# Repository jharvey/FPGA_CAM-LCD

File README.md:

# FPGA_CAM-LCD: single-board FPGA monocular

A hand-held monocular on one PCB, based on a stripped ULX3S:

- Lattice ECP5-85F FPGA, SDRAM, flash, ESP32-S3 (WiFi, USB, programming), SD card
- OV7670 camera module on the scene side, Newhaven 2.1" round TFT (NHD-2.1-480480AF-ASXP) on the eye side
- Three 18650 cells, each hot-swappable through its own quarter-turn cap, plus USB-C charging
- 3D-printed case with a 1/4-20 tripod thread

## Where things stand (2026-11-27)

| Area | State |
|---|---|
| Schematic | Frozen, with later additions listed in `doc/constraints/schematic_freeze.md` |
| PCB | Routed. KiCad DRC: 0 errors, 0 unconnected (branch `merged-board`) |
| Battery end blocks | One common machined aluminium block at all three cells, MS3181-16 bayonet caps. Mounting-hole pattern still under review |
| Case | Draft 4 modelled (not printed yet): two shells, two cell cradles, snap-in buttons, camera screwed to the lid |
| Ordering | **Not ready.** See "Open before ordering" in `ROADMAP.md` |
| FPGA and software | Written and tested in simulation only, no board exists. One bitstream (camera to TFT, overlay with text and graphics, sensor bridge) that meets timing; the ESP32 software (hub, pages, phone page) runs under MicroPython on a PC. `doc/DEVELOPER_GUIDE.md` |

**Try it without hardware** (Python 3): `python firmware/sim/fcl_sim.py --web 8080`, then open `http://127.0.0.1:8080`.
Start reading at `doc/QUICK_START.md`.

## Branches

- `merged-board`: the newest board and case. Open `FCL.kicad_pro` here.
- `monocular-strip`: the long-running design branch. `merged-board` has not been merged back into it yet.
- `battery-blocks`, `j7-vertical-wip`: the two lines of work that were combined into `merged-board`. Kept for history.
- `master`: the original ULX3S files.

## Documents

| Document | What it covers |
|---|---|
| `ROADMAP.md` | Decisions, phase status, dated change log, open items |
| `AI_GUIDE.md` | Working rules for an AI assistant or a new contributor |
| `case/README.md` | How to print, assemble and regenerate the case; hardware list |
| `docs/mech/README.md` | Battery end block: machining drawing and editable models |
| `docs/mech/freecad/README.md`, `case/freecad/README.md` | The FreeCAD files |
| `doc/constraints/camera_display_pinmap.md` | FPGA pins for the display, camera and user I/O |
| `doc/constraints/schematic_freeze.md` | Schematic freeze record and what changed after it |
| `doc/BRINGUP.md` (`.pdf`) | First power-up checklist (first article): test points, rails, programming, stage-by-stage checks |
| `doc/PRODUCTION_TEST.md` | Short per-board check once the design is validated, compared with BRINGUP golden values |
| `doc/QUICK_START.md` (`.pdf`) | One page: buttons, pages, first use, the PC tools |
| `doc/USER_MANUAL.md` | Using the unit: buttons, the screen and its graphics, the Level / Height / Bearing / Survey pages, menu, phone page, updates over Wi-Fi, logging, calibration (pictures in `doc/manual/`) |
| `doc/TROUBLESHOOTING.md` | What to look at, by symptom |
| `doc/DEVELOPER_GUIDE.md` | Software layers, writing a page of your own, graphics, scripting from a PC, the phone page's addresses, FPGA builds and clocks, tests |
| `doc/lessons/README.md` | Six lessons with the simulator: readings, slopes, heights, the compass, a room plan, a page of your own |
| `doc/FIRMWARE_GUIDE.md` | Reference made from a simulator run: USB stream, dashboard, LCD overlay, commands (pictures in `doc/fw/`) |
| `fpga/prebuilt/` | Stored build outputs: the three bitstreams, intermediates, checksums, tool versions, timing, test logs. `python fpga/make_prebuilt.py --check` compares your build with them |
| `fpga/bridge/`, `fpga/osd/`, `fpga/full/` | FPGA bridge to the ESP32 (sensors, ADC, servos, buttons), the LCD overlay, and the full design with its whole-design simulation |
| `doc/PROBE_POINTS.md` | Bare-copper probe vias on the back: spare FPGA balls, spare ESP32 pins, key nets (map: `doc/probe_points.png`) |
| `doc/jlc_check_2026-11-22.md` | JLCPCB build check (a dated snapshot; see the note at its top) |
| `fpga/IO_REMAP.md`, `fpga/ESP32_PINS.md` | FPGA and ESP32 pin maps; the camera project's clocks and what was changed in it |
| `mechanical.kicad_sch` | Mechanical bill of materials (screws, caps, springs, printed and machined parts) |

`doc/MANUAL.md`, `doc/MINIMAL.md`, `doc/TODO.txt` and the other files in `doc/` come from the original ULX3S project and describe that board, not this one.

## Phase order (do not skip)

1. Cleanup / hierarchy (done / finishing)
2. Power input redesign (3×18650)
3. Camera + display connectors/sheets
4. Mechanical outline / placement
5. BOM + JLCPCB

## When unsure

- Ask before deleting anything on `power`, `usb`, `ram`, `flash`, or `wifi`.
- Prefer “mark for deletion” + commit message over silent large deletes.
- Reference `ROADMAP.md` for locked decisions.

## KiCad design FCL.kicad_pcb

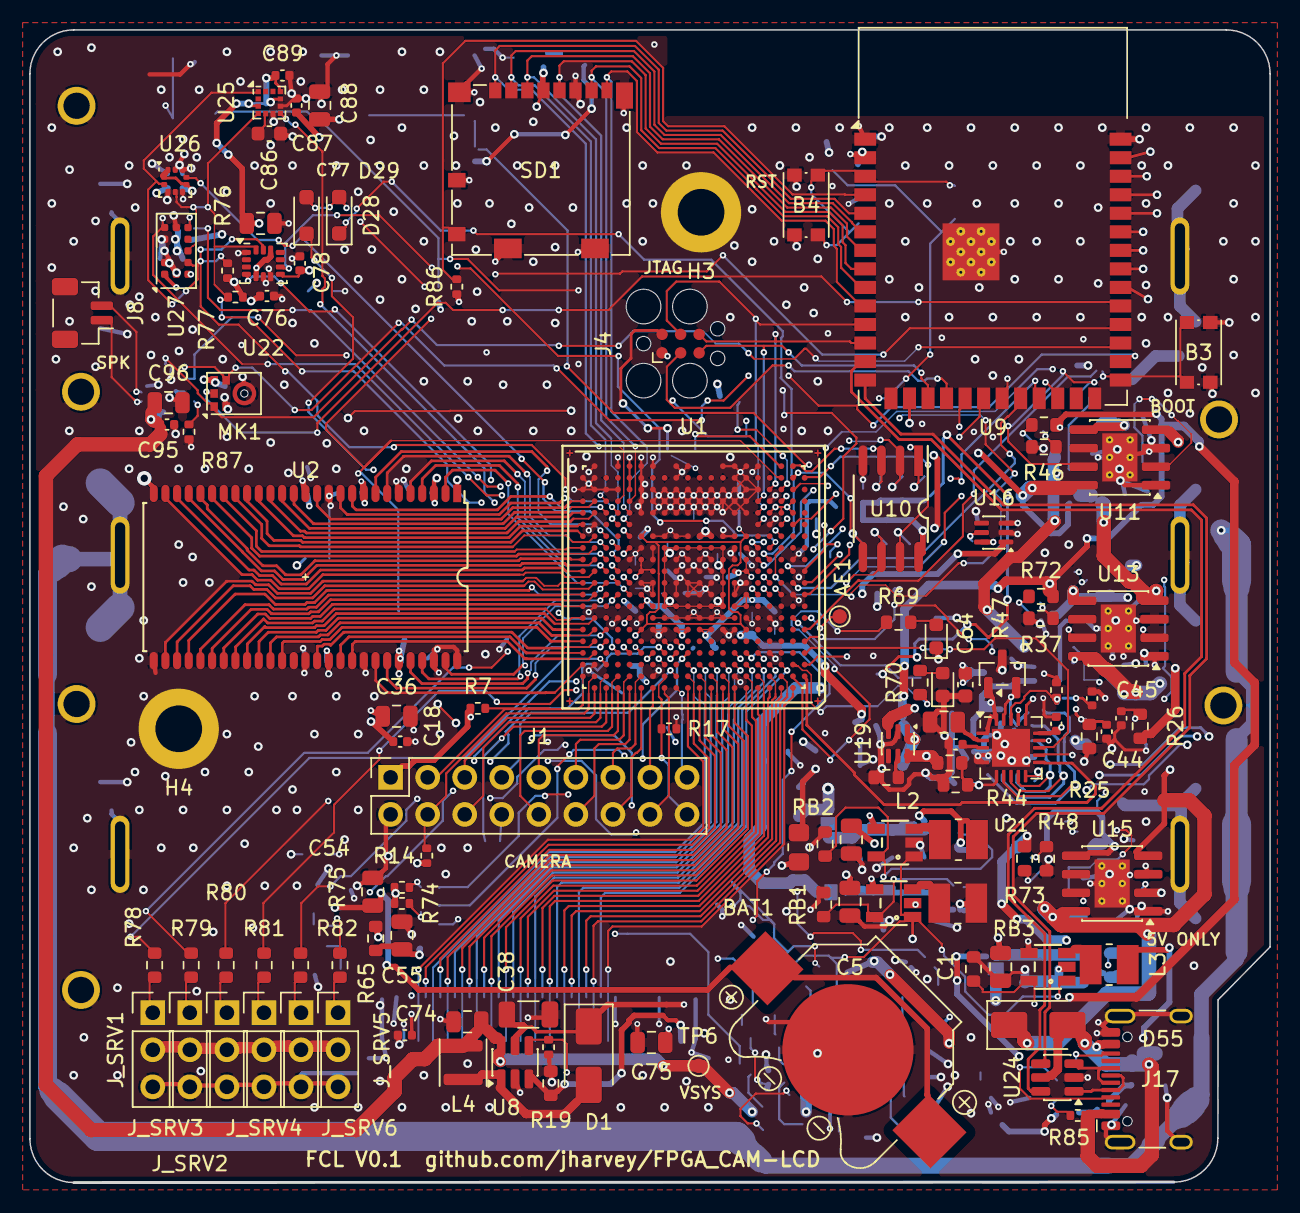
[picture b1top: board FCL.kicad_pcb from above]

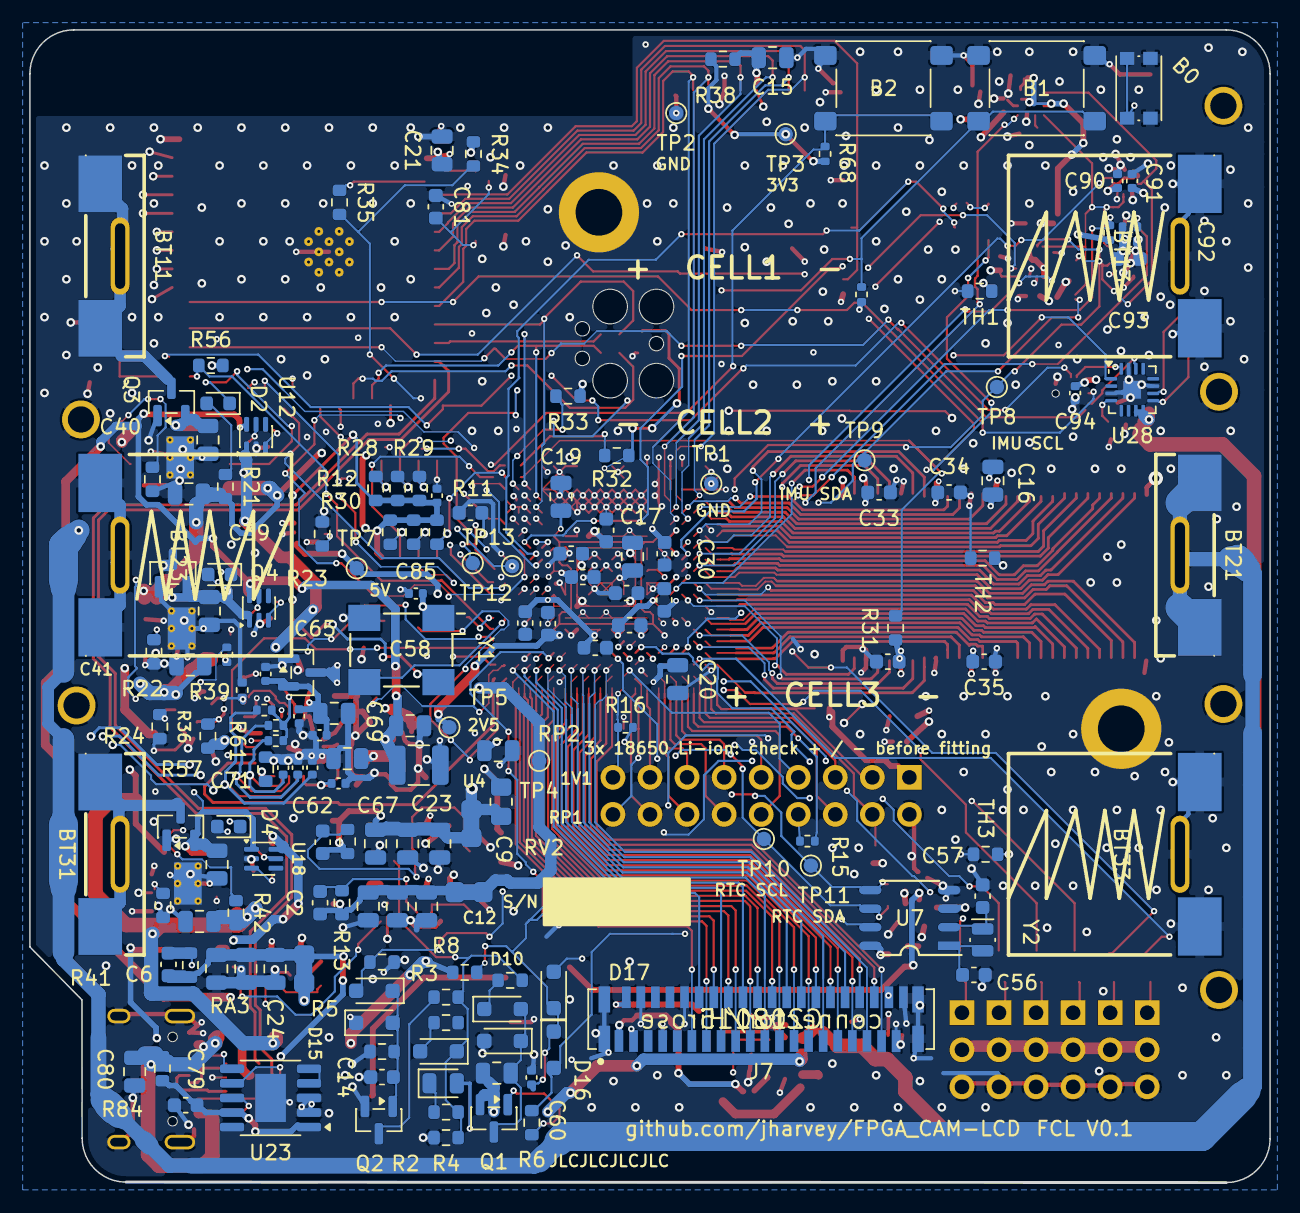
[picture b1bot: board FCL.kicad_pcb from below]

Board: 4 copper layers, 85.0 x 79.0 mm, 282 parts (169 on the bottom side), 238 nets.

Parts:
AE1: 433MHz; TestPoint_Pad_D1.0mm
B0: PWR; SW_Push_1P1T_NO_CK_KMR2
B1, B2: PTS645; SW_SPST_PTS645Sx43SMTR92
B3: BOOT; SW_Push_1P1T_NO_CK_KMR2
B4: RESET; SW_Push_1P1T_NO_CK_KMR2
BAT1: CR1225; Keystone_3000_1x12mm-CoinCell
BT11, BT21, BT31: MY-18650-04-J; BAT-TH_MY-18650-04-J
BT12, BT22, BT32: Battery block MS3181; FCL_BatteryBlock_Mount_MS3181
BT13, BT23, BT33: MY-18650-05-J; BAT-TH_MY-18650-05-J
C1, C3, C4, C5, C7, C8, C9, C11, C12, C15, C21, C54, C55: 22uF; C_0805_2012Metric
C2, C6, C10: 100pF; C_0603_1608Metric
C13, C16, C17, C19, C20, C22, C23, C24, C47, C77: 2.2uF; C_0805_2012Metric
C14, C86: 220nF; C_0603_1608Metric
C18, C44, C45, C59, C61, C62, C67, C70, C71, C72, C74, C76, C82, C83, C84, C85, C87, C89, C90, C91, C92, C94, C95: 100nF; C_0402_1005Metric
C25, C27, C28, C29, C30, C31, C32, C33, C34, C35, C48, C49, C50, C51, C52: 22nF; C_0603_1608Metric
C36, C37, C39, C40, C41, C42, C43, C46, C58, C63, C68, C69, C75, C80, C88, C96: 10uF; C_0805_2012Metric
C38: 4.7uF 50V; C_1206_3216Metric
C56, C57: 12pF; C_0603_1608Metric
C60: 220nF; C_0402_1005Metric
C64, C79, C81: 1uF; C_0603_1608Metric
C65: 1uF; C_0402_1005Metric
C73: 100uF 10V; C_1210_3225Metric
C78: 10nF; C_0402_1005Metric
C93: 4.7uF; C_0603_1608Metric
D1: SS14; D_SMA
D2, D3, D4, D53, D54: RED; LED_0603_1608Metric
D10, D13, D14, D16, D17, D28, D29: 1N914; D_SOD-323_HandSoldering
D11: RED; LED_0805_2012Metric
D12, D15: BAT54W; D_SOD-323_HandSoldering
D55: SS34; D_SMA
H3, H4: HOLE; MountingHole_3.2mm_M3_ISO14580_Pad
J1: OV7670_2x9; PinSocket_2x09_P2.54mm_Vertical
J4: CONN_02X03; Tag-Connect_TC2030-IDC-FP_2x03_P1.27mm_Vertical
J7: NHD-2.1-480480AF-ASXP; Hirose_FH12-40S-0.5SV_1x40-1MP_P0.50mm_Vertical
J8: Speaker; JST_SH_BM02B-SRSS-TB_1x02-1MP_P1.00mm_Vertical
J17: USB-C (USB 2.0, power + data); USB_C_Receptacle_HCTL_HC-TYPE-C-16P-01A
J_SRV1, J_SRV2, J_SRV3, J_SRV4, J_SRV5, J_SRV6: RC_SERVO; PinHeader_1x03_P2.54mm_Vertical
L1, L2, L3: 2.2uH; L_1008_1210
L4: 4.7uH; L_Sunlord_SWPA3015S
MK1: ICS-43434; InvenSense_ICS-43434-6_3.5x2.65mm
Q1: BC857; SOT-23
Q2: 2N7002; SOT-23
Q3, Q4, Q5: AO3401A; SOT-23
R1, R3, R4, R30: 4.7k; R_0603_1608Metric
R2: 18k; R_0603_1608Metric
R5: 2.2M; R_0603_1608Metric
R6, R8, R21, R29, R42, R69, R70, R78, R79, R80, R81, R82, R83, R84: 1k; R_0603_1608Metric
R7, R14, R74, R75, R76, R77: 4.7k; R_0402_1005Metric
R10: 120; R_0603_1608Metric
R11, R12, R27, R28: 10k; R_0603_1608Metric
R13, R31, R32, R33, R34, R56: 15k; R_0603_1608Metric
R15: 33R; R_0402_1005Metric
R16, R17, R43, R60, R61, R67, R68, R85, R86, R88, R89: 10k; R_0402_1005Metric
R18, R87: 100k; R_0402_1005Metric
R19: 2R0; R_0603_1608Metric
R20, R22, R41: 5.6k; R_0603_1608Metric
R23: 1k; R_0402_1005Metric
R24, R26: 47k; R_0603_1608Metric
R25, R36: 56k; R_0603_1608Metric
R35, R65: 560; R_0603_1608Metric
R37: 47k; R_0402_1005Metric
R38: 0.47; R_0603_1608Metric
R39: 56k; R_0402_1005Metric
R44: 100k; R_0603_1608Metric
R45: 68k; R_0603_1608Metric
R46, R47, R48, R51, R55, R57, R71, R72, R73: 0R; R_0603_1608Metric
RA1, RA2, RA3: 15k; R_0603_1608Metric
RB1: 18k; R_0603_1608Metric
RB2: 4.7k; R_0603_1608Metric
RB3: 3.3k; R_0603_1608Metric
RP1, RP2, RP3: 0; R_0805_Jumper_NC_NetTie
RV2, RV3: 0; R_0805_2012Metric_Pad1.20x1.40mm_HandSolder
SD1: 104031-0811; microSD_Molex_104031-0811_FCL
TH1, TH2, TH3: NTC 10k; R_0603_1608Metric
TP1, TP2: GND; TestPoint_Pad_D1.0mm
TP3: +3V3; TestPoint_Pad_D1.0mm
TP4: +1V1; TestPoint_Pad_D1.0mm
TP5: +2V5; TestPoint_Pad_D1.0mm
TP6: VSYS; TestPoint_Pad_D1.0mm
TP7: +5V; TestPoint_Pad_D1.0mm
TP8: IMU_SCL; TestPoint_Pad_D1.0mm
TP9: IMU_SDA; TestPoint_Pad_D1.0mm
TP10: FPDI_SCL; TestPoint_Pad_D1.0mm
TP11: FPDI_SDA; TestPoint_Pad_D1.0mm
TP12: WIFI_TXD; TestPoint_Pad_D1.0mm
TP13: WIFI_RXD; TestPoint_Pad_D1.0mm
U1: LFE5U-85F-6BG381C; BGA-381_pitch0.8mm_dia0.4mm
U2: M12L2561616A-6TG2T; TSOP54
U3, U4, U5: TLV62569DBV; TSOT-25
U7: MCP7940NT; SOT96-1
U8: AP3032KTR-G1; SOT-23-6
U9: ESP32-S3-WROOM-1-N8R2; ESP32-S3-WROOM-1
U10: W25Q128JVSIQ; SOA008-150-208mil
U11, U13, U15: TP4056; SOIC-8-1EP_3.9x4.9mm_P1.27mm_EP2.41x3.3mm_ThermalVias
U12, U14, U16, U18, U19: LM66100DCKR; SOT-363_SC-70-6
U17: REF3025; SOT-23
U20: XC6206P332MR-G; SOT-23
U21: AD7689BCPZRL7; LFCSP-20-1EP_4x4mm_P0.5mm_EP2.6x2.6mm
U22: ICM-42688-P; LGA-14_3x2.5mm_P0.5mm_LayoutBorder3x4y
U23: CH224K; SSOP-10-1EP_3.9x4.9mm_P1mm_EP2.1x3.3mm
U24: USBLC6-2SC6; SOT-23-6
U25: LIS2MDL; LGA-12_2x2mm_P0.5mm
U26: LPS22DF; ST_HLGA-10_2x2mm_P0.5mm_LayoutBorder3x2y
U27: VL53L1CXV0FY/1; ST_VL53L1x
U28: MAX98357A; TQFN-16-1EP_3x3mm_P0.5mm_EP1.23x1.23mm
Y1: SG-8101CA 25MHz; Crystal_SMD_7050_4Pads
Y2: 32768Hz; Crystal_SMD_MicroCrystal_CC8V-T1A-2Pin_2.0x1.2mm

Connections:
2V5_3V3: C47.1, C48.1, C49.1, RV2.2, RV3.1, U1.F9 (VCCio0), U1.F10 (VCCio0), U1.H6 (VCCio7), U1.H7 (VCCio7), U1.J6 (VCCio7)
+1V1: C17.1, C27.1, C28.1, RP1.2, TP4.1 (1_1), U1.H8 (VCC), U1.H9 (VCC), U1.H10 (VCC), U1.H11 (VCC), U1.H12 (VCC), U1.H13 (VCC), U1.J8 (VCC), U1.J13 (VCC), U1.K8 (VCC), U1.K13 (VCC), U1.L8 (VCC), U1.L13 (VCC), U1.M8 (VCC), U1.M13 (VCC), U1.N8 (VCC), U1.N9 (VCC), U1.N10 (VCC), U1.N11 (VCC), U1.N12 (VCC), U1.N13 (VCC)
+2V5: C19.1, C29.1, C30.1, RP2.2, RV2.1, TP5.1 (1_1), U1.F6 (VCCAUX), U1.F15 (VCCAUX), U1.P6 (VCCAUX), U1.P15 (VCCAUX)
+3V3: C16.1, C18.1, C20.1, C21.1, C25.1, C31.1, C32.1, C33.1, C34.1, C35.1, C36.1, C50.1, C51.1, C52.1, C72.1, C74.1, C75.1, C76.1, C77.1, C78.1, C84.1, C85.1, C87.1, C88.1, C89.1, C90.1, C91.1, C92.1, C93.1, C94.1, D11.2 (A), D14.1 (K), J1.1, J4.2, J7.3, J7.38, MK1.5 (VDD), R7.1, R11.1, R12.1, R14.1, R16.1, R27.1, R28.1, R29.1, R30.1, R31.1, R32.1, R33.1, R34.1, R38.2, R56.1, R65.1, R67.1, R68.1, R74.1, R75.1, R76.1, R77.2, R86.1, R88.1, R89.1, RP3.2, RV3.2, TP3.1 (1_1), U1.F11 (VCCio1), U1.F12 (VCCio1), U1.H14 (VCCio2), U1.H15 (VCCio2), U1.J15 (VCCio2), U1.L6 (VCCio6), U1.L7 (VCCio6), U1.L14 (VCCio3), U1.L15 (VCCio3), U1.M6 (VCCio6), U1.M15 (VCCio3), U1.P9 (VCCio8), U1.P10 (VCCio8), U1.T2 (SN/CSn), U1.T3 (WRITEn), U1.T4 (CFG_1), U1.U2 (CS1n), U2.1 (VDD), U2.3 (VDDQ), U2.9 (VDDQ), U2.14 (VDD), U2.27 (VDD), U2.43 (VDDQ), U2.49 (VDDQ), U9.2 (3V3), U10.8 (VCC), U21.15 (VIO), U22.5 (VDDIO), U22.8 (VDD), U22.12 (AP_CS), U25.3 (~CS), U25.9 (Vdd), U25.10 (Vdd_IO), U26.1 (Vdd_IO), U26.6 (~CS), U26.10 (VDD), U27.1 (AVDDVCSEL), U27.11 (AVDD), Y1.1 (EN), Y1.4 (Vdd)
+5V: C39.1, C41.1, C43.1, D55.1 (K), R21.1, R23.1, R42.1, TP7.1 (1_1), U11.4 (V_{CC}), U11.8 (CE), U13.4 (V_{CC}), U13.8 (CE), U15.4 (V_{CC}), U15.8 (CE), U16.1 (VIN)
/camera/XCLK_J: J1.8, R15.1
/display/LCD_BL_A: C38.1, D1.1 (K), J7.2, U8.5 (V_{OUT})
/display/LCD_BL_K: J7.1, R19.1, U8.3 (FB)
/display/LCD_BL_SW: D1.2 (A), L4.1, U8.1 (SW)
/flash/FLASH_MISO: R28.2, U1.V2 (D1/MISO), U10.2 (MISO)
/flash/FLASH_MOSI: R27.2, U1.W2 (D0/MOSI), U10.5 (MOSI)
/flash/FLASH_SCK: R29.2, U1.U3 (CCLK), U10.6 (SCK)
/flash/FLASH_nCS: R30.2, U1.R2 (CSSPIN), U10.1 (~CS)
/flash/FLASH_nHOLD: R12.2, U1.W1 (D3/HOLDn), U10.7 (~HOLD)
/flash/FLASH_nWP: R11.2, U1.Y2 (D2/WPn), U10.3 (~WP)
/flash/FPGA_DONE: R32.2, U1.Y3 (DONE)
/flash/FPGA_INITN: R33.2, U1.V3 (INITn)
/flash/FPGA_PROGRAMN: D28.2 (A), D29.2 (A), R31.2, U1.W3 (PROGRAMn)
/imu/MAG_C1: C86.1, U25.5 (C1)
/peripherals/SPK_N: J8.2, U28.10 (OUTN)
/peripherals/SPK_P: J8.1, U28.9 (OUTP)
/power/BAT1_CE: R71.1, U12.3 (~CE)
/power/BAT2_CE: R72.1, U14.3 (~CE)
/power/BAT3_CE: R73.1, U18.3 (~CE)
/power/CELL1_RAW: BT11.1 (Pin_1_1), Q3.3 (D)
/power/CELL2_RAW: BT21.1 (Pin_1_1), Q4.3 (D)
/power/CELL3_RAW: BT31.1 (Pin_1_1), Q5.3 (D)
/power/CHG1_CHRGn: D2.1 (K), U11.7 (~CHRG)
/power/CHG2_CHRGn: D3.1 (K), U13.7 (~CHRG)
/power/CHG3_CHRGn: D4.1 (K), U15.7 (~CHRG)
/power/FB1: C2.2, RA1.2, RB1.2, U3.5 (FB)
/power/FB2: C10.2, RA2.2, RB2.2, U4.5 (FB)
/power/FB3: C6.2, RA3.2, RB3.2, U5.5 (FB)
/power/FTDI_nSUSPEND: D12.2 (A), R10.1
/power/HOLD: D11.1 (K), R4.1
/power/L1: L1.1, U3.3 (LX)
/power/L2: L2.1, U4.3 (LX)
/power/L3: L3.1, U5.3 (LX)
/power/LED1_A: D2.2 (A), R21.2
/power/LED2_A: D3.2 (A), R23.2
/power/LED3_A: D4.2 (A), R42.2
/power/OSCI_32k: C56.2, U7.1 (OSCI), Y2.2
/power/OSCO_32k: C57.2, U7.2 (OSCO), Y2.1
/power/P1V1: C2.1, C3.1, C4.1, C22.1, L1.2, RA1.1, RP1.1
/power/P2V5: C10.1, C11.1, C12.1, C23.1, L2.2, RA2.1, RP2.1
/power/P3V3: C6.1, C7.1, C8.1, C24.1, L3.2, RA3.1, RP3.1
/power/PROG1: R20.1, U11.2 (PROG)
/power/PROG2: R22.1, U13.2 (PROG)
/power/PROG3: R41.1, U15.2 (PROG)
/power/PWREN: D12.1 (K), R1.2, R2.1, R4.2, R8.1, U3.1 (EN), U4.1 (EN), U5.1 (EN)
/power/RTCVDD: C55.1, R65.2, U7.8 (VDD)
/power/SHD: Q2.3 (D), R8.2
/power/SHUT: C14.1, D14.2 (A), D15.1 (K), Q2.1 (G), R5.1
/power/TEMP_BAT_CELL1: C62.1, R43.2, TH1.1, U21.7 (IN5)
/power/TEMP_BAT_CELL2: C82.1, R60.2, TH2.1, U21.8 (IN6)
/power/TEMP_BAT_CELL3: C83.1, R61.2, TH3.1, U21.9 (IN7)
/power/VADC: C61.1, C65.1, C69.1, C71.1, U17.1 (IN), U20.2 (VO), U21.1 (VDD), U21.20 (VDD)
/power/VBAT: BAT1.1 (+), C54.1, U7.3 (~INT)
/power/VBAT1: C40.1, Q3.2 (S), R24.1, U11.5 (BAT), U12.1 (VIN)
/power/VBAT1_SENSE: C44.1, R24.2, R25.1, U21.16 (IN0)
/power/VBAT2: C42.1, Q4.2 (S), R26.1, U13.5 (BAT), U14.1 (VIN)
/power/VBAT2_SENSE: C45.1, R26.2, R36.1, U21.17 (IN1)
/power/VBAT3: C46.1, Q5.2 (S), R37.1, U15.5 (BAT), U18.1 (VIN)
/power/VBAT3_SENSE: C59.1, R37.2, R39.1, U21.18 (IN2)
/power/VREF_2V5: C68.1, U21.2 (REF)
/power/VREF_SENSE: R43.1, R60.1, R61.1, U17.2 (OUT), U21.19 (IN3)
/power/VSYS_SENSE: C67.1, R44.2, R45.1, U21.6 (IN4)
/power/WAKE: D10.1 (K), R1.1
/power/WAKEUPn: D16.2 (A), R6.2, U7.7 (CLKO)
/power/WKUP: C13.2, D10.2 (A), D13.1 (K), Q1.3 (C)
/power/WKn: Q1.1 (B), R6.1
/usb/ANT_433MHz: AE1.1 (A_1), U1.G1 (PCLKC6_0)
/usbc_pd/PD_CC1: J17.A5 (CC1), U23.7 (CC1)
/usbc_pd/PD_CC2: J17.B5 (CC2), U23.6 (CC2)
/usbc_pd/PD_VDD: C79.2, R84.2, U23.1 (VDD), U23.9 (CFG1)
/usbc_pd/USB_C_DN: J17.A7 (D-), J17.B7 (D-), U24.1 (I/O1)
/usbc_pd/USB_C_DP: J17.A6 (D+), J17.B6 (D+), U24.3 (I/O2)
/usbc_pd/VBUS_C: C80.1, D55.2 (A), J17.A4 (VBUS), J17.A9 (VBUS), J17.B4 (VBUS), J17.B9 (VBUS), R84.1, R85.1, U24.5 (VBUS)
/wifi/SD3V3: C15.1, R38.1, SD1.4 (VCC)
/wifi/WIFIEN: B4.2, C81.1, R35.2, U9.3 (EN)
ADC_CNV: U1.B1 (PL35B), U21.11 (CNV)
ADC_DIN: U1.E1 (PL38D), U21.12 (DIN)
ADC_SCK: U1.D1 (PL38B), U21.13 (SCK)
ADC_SDO: U1.C1 (PL38A), U21.14 (SDO)
AMP_SD: R87.1, U9.24 (IO47), U28.4 (~SD_MODE)
BARO_INT: U1.M17 (PR53B), U26.7 (INT_DRDY)
BTN1n: B1.2, R67.2, U1.N5 (PL83B)
BTN2n: B2.2, R68.2, U1.M5 (PL77A)
BTN_PWRn: D17.2 (A), U1.D6 (PT6B)
CAM_XCLK: R15.2, U1.A18 (PT119A)
CLK_25MHz: U1.G2 (PCLKT6_1), Y1.3 (OUT)
FPDI_SCL: R74.2, TP10.1 (1_1), U1.E12 (GR_PCLK1_1), U7.6 (SCL)
FPDI_SDA: R75.2, TP11.1 (1_1), U1.D12 (GR_PCLK1_0), U7.5 (SDA)
GN0: J7.11, U1.A2 (PL35A)
GN1: J7.13, U1.B3 (PL14D)
GN2: J7.15, U1.C4 (PL14A)
GN3: J7.17, U1.A4 (PL11A)
GN4: J7.19, U1.B5 (PL11C)
GN5: J7.21, U1.C6 (PT11A)
GN6: J7.23, U1.A6 (PT4A)
GN7: J7.25, U1.A7 (PT18A)
GN8: J7.27, U1.B8 (PT15B)
GN9: J7.29, U1.C9 (PT54A)
GN10: J7.31, U1.A9 (GR_PCLK0_1)
GN11: J7.33, U1.B10 (GR_PCLK0_0)
GN12: J7.35, U1.C11 (PCLKC0_0)
GN13: J7.37, U1.A11 (PCLKC0_1)
GN14: J1.3, R7.2, U1.B20 (PT121B)
GN15: J1.5, U1.A19 (PT121A)
GN17: J1.17, R16.2, U1.A12 (PT76A)
GN21: J1.9, U1.A17 (PT116A)
GN22: J1.11, U1.B16 (PT110B)
GN23: J1.13, U1.B15 (PT105A)
GN24: J1.15, U1.A14 (PT83A)
GND: B0.2, B1.1, B2.1, B3.1, B4.1, BAT1.2 (-), BT12.1, BT13.1, BT22.1, BT23.1, BT32.1, BT33.1, C1.2, C3.2, C4.2, C5.2, C7.2, C8.2, C9.2, C11.2, C12.2, C14.2, C15.2, C16.2, C17.2, C18.2, C19.2, C20.2, C21.2, C22.2, C23.2, C24.2, C25.2, C27.2, C28.2, C29.2, C30.2, C31.2, C32.2, C33.2, C34.2, C35.2, C36.2, C37.2, C38.2, C39.2, C40.2, C41.2, C42.2, C43.2, C44.2, C45.2, C46.2, C47.2, C48.2, C49.2, C50.2, C51.2, C52.2, C54.2, C55.2, C56.1, C57.1, C58.2, C59.2, C60.2, C61.2, C62.2, C63.2, C64.2, C65.2, C67.2, C68.2, C69.2, C70.2, C71.2, C72.2, C73.2, C74.2, C75.2, C76.2, C77.2, C78.2, C79.1, C80.2, C81.2, C82.2, C83.2, C84.2, C85.2, C86.2, C87.2, C88.2, C89.2, C90.2, C91.2, C92.2, C93.2, C94.2, C95.2, C96.2, D13.2 (A), D53.1 (K), D54.1 (K), H3.1 (Pin_1_1), H4.1 (Pin_1_1), J1.2, J4.1, J7.4, J7.7, J7.10, J7.39, J7.40, J7.MP, J17.A1 (GND), J17.A12 (GND), J17.B1 (GND), J17.B12 (GND), J17.SH (SHIELD), J_SRV1.3, J_SRV2.3, J_SRV3.3, J_SRV4.3, J_SRV5.3, J_SRV6.3, MK1.2 (LR), MK1.3 (GND), Q2.2 (S), Q3.1 (G), Q4.1 (G), Q5.1 (G), R2.2, R5.2, R13.2, R17.2, R18.2, R19.2, R20.2, R22.2, R25.2, R36.2, R39.2, R41.2, R45.2, R46.2, R47.2, R48.2, R51.2, R55.2, R57.1, R87.2, RB1.1, RB2.1, RB3.1, SD1.6 (GND), SD1.GM1 (GND), SD1.GM2 (GND), SD1.GM3 (GND), SD1.GM4 (GND), SD1.GS4 (GND), TH1.2, TH2.2, TH3.2, TP1.1 (1_1), TP2.1 (1_1), U1.B7 (GND), U1.B14 (GND), U1.C19 (GND), U1.D4 (GND), U1.F7 (GND), U1.F8 (GND), U1.F13 (GND), U1.F14 (GND), U1.G4 (GND), U1.G6 (GND), U1.G7 (GND), U1.G8 (GND), U1.G9 (GND), U1.G10 (GND), U1.G11 (GND), U1.G12 (GND), U1.G13 (GND), U1.G14 (GND), U1.G15 (GND), U1.G17 (GND), U1.H19 (GND), U1.J2 (GND), U1.J7 (GND), U1.J9 (GND), U1.J10 (GND), U1.J11 (GND), U1.J12 (GND), U1.J14 (GND), U1.K6 (GND), U1.K7 (GND), U1.K9 (GND), U1.K10 (GND), U1.K11 (GND), U1.K12 (GND), U1.K14 (GND), U1.K15 (GND), U1.L9 (GND), U1.L10 (GND), U1.L11 (GND), U1.L12 (GND), U1.M2 (GND), U1.M7 (GND), U1.M9 (GND), U1.M10 (GND), U1.M11 (GND), U1.M12 (GND), U1.M14 (GND), U1.M16 (GND), U1.N6 (GND), U1.N7 (GND), U1.N14 (GND), U1.N15 (GND), U1.P7 (GND), U1.P8 (GND), U1.P11 (GND), U1.P12 (GND), U1.P13 (GND), U1.P14 (GND), U1.R4 (CFG_2), U1.R19 (GND), U1.T6 (VCCA0), U1.T7 (VCCHTX0_D0CH0), U1.T8 (VCCHRX0_D0CH0), U1.T9 (VCCHRX0_D0CH1), U1.T10 (VCCHTX0_D0CH1), U1.T11 (VCCHTX0_D1CH0), U1.T12 (VCCHRX0_D1CH0), U1.T13 (VCCHRX0_D1CH1), U1.T14 (VCCHTX0_D1CH1), U1.T15 (VCCA1), U1.U4 (CFG_0), U1.U6 (VCCA0), U1.U7 (GND), U1.U8 (GND), U1.U9 (GND), U1.U10 (GND), U1.U11 (GND), U1.U12 (GND), U1.U13 (GND), U1.U14 (GND), U1.U15 (VCCA1), U1.V5 (GND), U1.V6 (GND), U1.V7 (GND), U1.V8 (GND), U1.V9 (GND), U1.V10 (VCCAUXA0), U1.V11 (VCCAUXA0), U1.V12 (GND), U1.V13 (GND), U1.V14 (GND), U1.V15 (GND), U1.V16 (GND), U1.V17 (VCCAUXA1), U1.V18 (VCCAUXA1), U1.V19 (GND), U1.V20 (GND), U1.W6 (GND), U1.W7 (GND), U1.W12 (GND), U1.W15 (GND), U1.W16 (GND), U1.W19 (GND), U1.W20 (REFCLKN_D1), U1.Y5 (HDRXP0_D0CH0), U1.Y6 (HDRXN0_D0CH0), U1.Y7 (HDRXP0_D0CH1), U1.Y8 (HDRXN0_D0CH1), U1.Y11 (REFCLKP_D0), U1.Y12 (REFCLKN_D0), U1.Y14 (HDRXP0_D1CH0), U1.Y15 (HDRXN0_D1CH0), U1.Y16 (HDRXP0_D1CH1), U1.Y17 (HDRXN0_D1CH1), U1.Y19 (REFCLKP_D1), U2.6 (VSSQ), U2.12 (VSSQ), U2.28 (VSS), U2.41 (VSS), U2.46 (VSSQ), U2.52 (VSSQ), U2.54 (VSS), U3.2 (GND), U4.2 (GND), U5.2 (GND), U7.4 (VSS), U8.2 (GND), U9.1 (GND), U9.40 (GND), U9.41 (GND), U10.4 (GND), U11.1 (TEMP), U11.3 (GND), U11.9 (EPAD), U12.2 (GND), U13.1 (TEMP), U13.3 (GND), U13.9 (EPAD), U14.2 (GND), U15.1 (TEMP), U15.3 (GND), U15.9 (EPAD), U16.2 (GND), U17.3 (GND), U18.2 (GND), U19.2 (GND), U20.1 (GND), U21.4 (GND), U21.5 (GND), U21.21 (EPAD), U22.1 (AP_AD0/AP_SDO), U22.6 (GND), U22.7 (RESV_GND), U23.2 (CFG2), U23.3 (CFG3), U23.11 (GND), U24.2 (GND), U25.6 (GND), U25.8 (GND), U26.3 (GND), U26.5 (SA0), U26.8 (GND_IO), U26.9 (GND), U27.2 (AVSSVCSEL), U27.3 (GND), U27.4 (GND), U27.6 (GND), U27.12 (GND), U28.3 (GND), U28.11 (GND), U28.15 (GND), U28.17 (PAD), Y1.2 (GND)
GP0: J7.12, U1.C3 (PL17C)
GP1: J7.14, U1.A3 (PL14C)
GP2: J7.16, U1.B4 (PL14B)
GP3: J7.18, U1.C5 (PL11D)
GP4: J7.20, U1.A5 (PL11B)
GP5: J7.22, U1.B6 (PT4B)
GP6: J7.24, U1.C7 (PT11B)
GP7: J7.26, U1.C8 (PT15A)
GP8: J7.28, U1.A8 (PT18B)
GP9: J7.30, U1.B9 (PT58A)
GP10: J7.32, U1.C10 (PT58B)
GP11: J7.34, U1.A10 (PCLKT0_1)
GP12: J7.36, U1.B11 (PCLKT0_0)
GP13: R18.1, U1.G16 (PR17C), U8.4 (CTRL)
GP14: J1.4, R14.2, U1.B19 (PT119B)
GP15: J1.6, U1.B18 (PT116B)
GP16: J1.18, R17.1, U1.B13 (PT78A)
GP17: J1.7, U1.B12 (PCLKT1_0)
GP21: J1.10, U1.B17 (PT114A)
GP22: J1.12, U1.A16 (PT110A)
GP23: J1.14, U1.A15 (PT103A)
GP24: J1.16, U1.A13 (PT76B)
I2S_BCLK: MK1.4 (SCK), U9.28 (IO35), U28.16 (BCLK)
I2S_MIC: MK1.6 (SD), U9.31 (IO38)
I2S_SPK: U9.30 (IO37), U28.1 (DIN)
I2S_WS: MK1.1 (WS), U9.29 (IO36), U28.14 (LRCLK)
IMU_INT1: U1.K16 (PR29A), U22.4 (INT1)
IMU_INT2: U1.N4 (PL83C), U22.9 (INT2/FSYNC/CLKIN)
IMU_SCL: R76.2, TP8.1 (1_1), U1.P16 (VREF1_3), U22.13 (AP_SCL/AP_SCLK), U25.1 (SCL/SPC), U26.2 (SCL), U27.10 (SCL)
IMU_SDA: R77.1, TP9.1 (1_1), U1.K17 (PR29B), U22.14 (AP_SDA/AP_SDIO), U25.4 (SDA/SDI/SDO), U26.4 (SDA), U27.9 (SDA)
JTAG_TCK: J4.4, U1.T5 (TCK), U9.11 (IO18)
JTAG_TDI: J4.3, U1.R5 (TDI), U9.18 (IO10)
JTAG_TDO: J4.6, U1.V4 (TDO), U9.12 (IO8)
JTAG_TMS: J4.5, U1.U5 (TMS), U9.17 (IO9)
LED0: R69.1, U1.B2 (VREF1_7)
LED1: R70.1, U1.C2 (PL35D)
MAG_DRDY: U1.L17 (PR50B), U25.7 (DRDY)
unnamed: D53.2 (A), R69.2
unnamed: D54.2 (A), R70.2
unnamed: J_SRV1.1, R78.2
unnamed: J_SRV2.1, R79.2
unnamed: J_SRV3.1, R80.2
unnamed: J_SRV4.1, R81.2
unnamed: J_SRV5.1, R82.2
unnamed: J_SRV6.1, R83.2
unnamed: R46.1, U12.5 (ST)
unnamed: R47.1, U14.5 (ST)
unnamed: R51.1, U16.5 (ST)
unnamed: R48.1, U18.5 (ST)
unnamed: R55.1, U19.5 (ST)
unnamed: R57.2, U21.10 (COM)
unnamed: C70.1, U21.3 (REFIN)
unnamed: U23.4 (DP), U23.5 (DM)
unnamed: R85.2, U23.8 (VBUS)
PWRBTn: B0.1, C60.1, D16.1 (K), D17.1 (K), D28.1 (K), R3.2
SDRAM_A0: U1.M20 (PCLKC3_1), U2.23 (A0)
SDRAM_A1: U1.M19 (PCLKC3_0), U2.24 (A1)
SDRAM_A2: U1.L20 (PCLKT3_1), U2.25 (A2)
SDRAM_A3: U1.L19 (PCLKT3_0), U2.26 (A3)
SDRAM_A4: U1.K20 (PCLKC2_0), U2.29 (A4)
SDRAM_A5: U1.K19 (PCLKC2_1), U2.30 (A5)
SDRAM_A6: U1.K18 (PR41D), U2.31 (A6)
SDRAM_A7: U1.J20 (PCLKT2_0), U2.32 (A7)
SDRAM_A8: U1.J19 (PCLKT2_1), U2.33 (A8)
SDRAM_A9: U1.H20 (PR41B), U2.34 (A9)
SDRAM_A10: U1.N19 (PR83A), U2.22 (A10)
SDRAM_A11: U1.G20 (PR38D), U2.35 (A11)
SDRAM_A12: U1.G19 (GR_PCLK2_1), U2.36 (A12)
SDRAM_BA0: U1.P19 (PR83C), U2.20 (BA0)
SDRAM_BA1: U1.N20 (PR83B), U2.21 (BA1)
SDRAM_CKE: U1.F20 (PR38C), U2.37 (CKE)
SDRAM_CLK: U1.F19 (PR38B), U2.38 (CLK)
SDRAM_D0: U1.J16 (PR20D), U2.2 (DQ0)
SDRAM_D1: U1.L18 (GR_PCLK3_1), U2.4 (DQ1)
SDRAM_D2: U1.M18 (PR50D), U2.5 (DQ2)
SDRAM_D3: U1.N18 (PR53C), U2.7 (DQ3)
SDRAM_D4: U1.P18 (PR83D), U2.8 (DQ4)
SDRAM_D5: U1.T18 (PR89D), U2.10 (DQ5)
SDRAM_D6: U1.T17 (GPLL0C_IN), U2.11 (DQ6)
SDRAM_D7: U1.U20 (PR86D), U2.13 (DQ7)
SDRAM_D8: U1.E19 (PR35D), U2.42 (DQ8)
SDRAM_D9: U1.D20 (VREF1_2), U2.44 (DQ9)
SDRAM_D10: U1.D19 (PR35B), U2.45 (DQ10)
SDRAM_D11: U1.C20 (PR35A), U2.47 (DQ11)
SDRAM_D12: U1.E18 (PR14C), U2.48 (DQ12)
SDRAM_D13: U1.F18 (PR14D), U2.50 (DQ13)
SDRAM_D14: U1.J18 (GR_PCLK2_0), U2.51 (DQ14)
SDRAM_D15: U1.J17 (PR20C), U2.53 (DQ15)
SDRAM_DQM0: U1.U19 (PR89C), U2.15 (DQML)
SDRAM_DQM1: U1.E20 (PR38A), U2.39 (DQMH)
SDRAM_nCAS: U1.T19 (PR89A), U2.17 (~CAS)
SDRAM_nCS: U1.P20 (PR86A), U2.19 (~CS)
SDRAM_nRAS: U1.R20 (PR86B), U2.18 (~RAS)
SDRAM_nWE: U1.T20 (PR86C), U2.16 (~WE)
SD_CD: R86.2, SD1.10 (SW-2), U9.4 (IO4)
SD_CLK: SD1.5 (CLK), U1.T16 (PR77A), U9.8 (IO15)
SD_CMD: SD1.3 (CMD), U1.R17 (PR56D), U9.7 (IO7)
SD_D0: SD1.7 (DAT0), U1.U16 (GPLL0T_IN), U9.9 (IO16)
SD_D1: SD1.8 (DAT1), U1.R16 (PR56C), U9.10 (IO17)
SD_D2: SD1.1 (DAT2), U1.U17 (PR92B), U9.5 (IO5)
SD_D3: SD1.2 (CD/DAT3), U1.U18 (PR92A), U9.6 (IO6)
SERVO_V: J_SRV1.2, J_SRV2.2, J_SRV3.2, J_SRV4.2, J_SRV5.2, J_SRV6.2
SHUTDOWN: D15.2 (A), R13.1, U1.D11 (PCLKT1_1)
SRV_PWM1: R78.1, U1.C18 (PR11A)
SRV_PWM2: R79.1, U1.D17 (PR11B)
SRV_PWM3: R80.1, U1.D16 (PT112B)
SRV_PWM4: R81.1, U1.D15 (PT107A)
SRV_PWM5: R82.1, U1.D14 (PT85A)
SRV_PWM6: R83.1, U1.D13 (PT80A)
TOF_INT: R89.2, U1.N17 (PR56A), U27.7 (GPIO1)
TOF_XSHUT: R88.2, U1.N16 (PR53A), U27.5 (XSHUT)
USB_DN: U9.13 (USB_D-), U24.6 (I/O1)
USB_DP: U9.14 (USB_D+), U24.4 (I/O2)
USER_PROGRAMN: D29.1 (K), U1.M4 (PL83A)
VBAT_OR: C58.1, C73.1, R71.2, R72.2, R73.2, U12.6 (VOUT), U14.6 (VOUT), U18.6 (VOUT), U19.1 (VIN)
VSYS: C1.1, C5.1, C9.1, C13.1, C37.1, C63.1, C64.1, C95.1, C96.1, L4.2, Q1.2 (E), R3.1, R44.1, TP6.1 (1_1), U3.4 (VIN), U4.4 (VIN), U5.4 (VIN), U8.6 (V_{IN}), U16.3 (~CE), U16.6 (VOUT), U19.3 (~CE), U19.6 (VOUT), U20.3 (VI), U28.7 (VDD), U28.8 (VDD)
WIFI_EN: R34.2, R35.1, U1.N3 (PL86A)
WIFI_GPIO0: B3.2, R56.2, U1.F1 (PCLKC6_1), U9.27 (IO0)
WIFI_GPIO13: U1.K1 (PL53D), U9.21 (IO13)
WIFI_GPIO14: U1.K2 (PL53A), U9.22 (IO14)
WIFI_GPIO21: U1.J1 (PL53B), U9.23 (IO21)
WIFI_RXD: TP13.1 (1_1), U1.L2 (PL86D), U9.20 (IO12)
WIFI_TXD: TP12.1 (1_1), U1.L1 (PL65C), U9.19 (IO11)

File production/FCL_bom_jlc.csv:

Comment,Designator,Footprint,LCSC
PWR/BOOT/RESET,"B0,B3,B4",SW_Push_1P1T_NO_CK_KMR2,C269272
PTS645,"B1,B2",SW_SPST_PTS645Sx43SMTR92,C285463
CR1225,BAT1,Keystone_3000_1x12mm-CoinCell,C238097
MY-18650-04-J,"BT11,BT21,BT31",BAT-TH_MY-18650-04-J,C19184125
MY-18650-05-J,"BT12,BT22,BT32",BAT-TH_MY-18650-05-J,C19184124
22uF,"C1,C11,C12,C15,C21,C3,C4,C5,C54,C55,C7,C8,C9",C_0805_2012Metric,C45783
100pF,"C10,C2,C6",C_0603_1608Metric,C14858
2.2uF,"C13,C16,C17,C19,C20,C22,C23,C24,C47,C77",C_0805_2012Metric,C108719
220nF,"C14,C86",C_0603_1608Metric,C21120
100nF,"C18,C44,C45,C59,C61,C62,C67,C70,C71,C72,C74,C76,C82,C83,C84,C85,C87,C89,C90,C91,C92,C94,C95",C_0402_1005Metric,C1525
22nF,"C25,C27,C28,C29,C30,C31,C32,C33,C34,C35,C48,C49,C50,C51,C52",C_0603_1608Metric,C21122
10uF,"C36,C37,C39,C40,C41,C42,C43,C46,C58,C63,C68,C69,C75,C80,C88,C96",C_0805_2012Metric,C15850
4.7uF 50V,C38,C_1206_3216Metric,C29823
12pF,"C56,C57",C_0603_1608Metric,C182482
220nF,C60,C_0402_1005Metric,C16772
1uF,"C64,C79,C81",C_0603_1608Metric,C15849
1uF,C65,C_0402_1005Metric,C52923
100uF 10V,C73,C_1210_3225Metric,C23742
10nF,C78,C_0402_1005Metric,C15195
4.7uF,C93,C_0603_1608Metric,C19666
SS14,D1,D_SMA,C2480
1N914,"D10,D13,D14,D16,D17,D28,D29",D_SOD-323_HandSoldering,C2128
RED,D11,LED_0805_2012Metric,C84256
BAT54W,"D12,D15",D_SOD-323_HandSoldering,C12744
RED,"D2,D3,D4,D53,D54",LED_0603_1608Metric,C2286
SS34,D55,D_SMA,C8678
OV7670_2x9,J1,PinSocket_2x09_P2.54mm_Vertical,C71956
"USB-C (USB 2.0, power + data)",J17,USB_C_Receptacle_HCTL_HC-TYPE-C-16P-01A,C2894897
NHD-2.1-480480AF-ASXP,J7,Hirose_FH12-40S-0.5SH_1x40-1MP_P0.50mm_Horizontal,C202114
Speaker,J8,JST_SH_BM02B-SRSS-TB_1x02-1MP_P1.00mm_Vertical,C160388
2.2uH,"L1,L2,L3",L_1008_1210,C285758
4.7uH,L4,L_Sunlord_SWPA3015S,C19398
ICS-43434,MK1,InvenSense_ICS-43434-6_3.5x2.65mm,C5656610
BC857,Q1,SOT-23,C181146
2N7002,Q2,SOT-23,C8545
AO3401A,"Q3,Q4,Q5",SOT-23,C15127
4.7k,"R1,R3,R30,R4,RB2",R_0603_1608Metric,C23162
120,R10,R_0603_1608Metric,C22787
10k,"R11,R12,R27,R28",R_0603_1608Metric,C25804
15k,"R13,R31,R32,R33,R34,R56,RA1,RA2,RA3",R_0603_1608Metric,C22809
4.7k,"R14,R7,R74,R75,R76,R77",R_0402_1005Metric,C25900
33R,R15,R_0402_1005Metric,C25105
10k,"R16,R17,R43,R60,R61,R67,R68,R85,R86,R88,R89",R_0402_1005Metric,C25744
100k,"R18,R87",R_0402_1005Metric,C25741
2R0,R19,R_0603_1608Metric,C22977
18k,"R2,RB1",R_0603_1608Metric,C25810
5.6k,"R20,R22,R41",R_0603_1608Metric,C23189
1k,"R21,R29,R42,R6,R69,R70,R8,R84",R_0603_1608Metric,C21190
1k,R23,R_0402_1005Metric,C11702
47k,"R24,R26",R_0603_1608Metric,C25819
56k,"R25,R36",R_0603_1608Metric,C23206
560,"R35,R65",R_0603_1608Metric,C23204
47k,R37,R_0402_1005Metric,C25792
0.47,R38,R_0603_1608Metric,C158884
56k,R39,R_0402_1005Metric,C25796
100k,R44,R_0603_1608Metric,C25803
68k,R45,R_0603_1608Metric,C23231
0R,"R46,R47,R48,R51,R55,R57,R71,R72,R73",R_0603_1608Metric,C21189
2.2M,R5,R_0603_1608Metric,C22938
3.3k,RB3,R_0603_1608Metric,C22978
0,RV3,R_0805_2012Metric_Pad1.20x1.40mm_HandSolder,C112378
104031-0811,SD1,microSD_Molex_104031-0811_FCL,C585350
NTC 10k,"TH1,TH2,TH3",R_0603_1608Metric,C13564
W25Q128JVSIQ,U10,SOA008-150-208mil,C113767
TP4056,"U11,U13,U15",SOIC-8-1EP_3.9x4.9mm_P1.27mm_EP2.41x3.3mm_ThermalVias,C16581
LM66100DCKR,"U12,U14,U16,U18,U19",SOT-363_SC-70-6,C2869734
REF3025,U17,SOT-23,C96625
M12L2561616A-6TG2T,U2,TSOP54,C492195
XC6206P332MR-G,U20,SOT-23,C5446
AD7689BCPZRL7,U21,LFCSP-20-1EP_4x4mm_P0.5mm_EP2.6x2.6mm,C706705
ICM-42688-P,U22,LGA-14_3x2.5mm_P0.5mm_LayoutBorder3x4y,C1850418
CH224K,U23,SSOP-10-1EP_3.9x4.9mm_P1mm_EP2.1x3.3mm,C970725
USBLC6-2SC6,U24,SOT-23-6,C7519
LIS2MDL,U25,LGA-12_2x2mm_P0.5mm,C919695
LPS22DF,U26,ST_HLGA-10_2x2mm_P0.5mm_LayoutBorder3x2y,C3253714
VL53L1CXV0FY/1,U27,ST_VL53L1x,C190004
MAX98357A,U28,TQFN-16-1EP_3x3mm_P0.5mm_EP1.23x1.23mm,C910544
TLV62569DBV,"U3,U4,U5",TSOT-25,C141836
MCP7940NT,U7,SOT96-1,C148052
AP3032KTR-G1,U8,SOT-23-6,C264086
ESP32-S3-WROOM-1-N8R2,U9,ESP32-S3-WROOM-1,C2913204
SG-8101CA 25MHz,Y1,Crystal_SMD_7050_4Pads,C390569
32768Hz,Y2,Crystal_SMD_MicroCrystal_CC8V-T1A-2Pin_2.0x1.2mm,C5366546
